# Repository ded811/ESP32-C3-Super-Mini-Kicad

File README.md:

# ESP32-C3 Super Mini KiCad Schematic

An ESP32-C3 Super Mini KiCad Schematic based on the AliExpress ESP32-C3 Super Mini boards, with the following improvements over the original design.

## Improvements

### Antenna — Major Improvement

| | Original | This Design |
|---|---|---|
| **Part** | CrossAir CA-C03 | Johanson 2450AT18A100 |
| **Frequency** | 2.7 GHz (mistuned for 2.4 GHz use) | 2.4 GHz (properly tuned) |
| **Matching Network** | None | Full T-network |
| **Placement** | Poorly placed | Optimised |

The original design used a **CrossAir CA-C03** antenna — a 2.7 GHz antenna pressed into service at 2.4 GHz with no matching network. The result is a mistuned antenna with poor radiation efficiency.

This design replaces it with a **Johanson 2450AT18A100**, a proper 2.4 GHz chip antenna, paired with a full T-network matching circuit using Murata 0201 RF components:

```
RF feed → 2.7 nH (series) → 1.0 pF (shunt to GND) → 3.9 nH (series) → Antenna
```

This ensures the antenna is correctly matched to 50 Ω at 2.4 GHz, maximising radiated power and receiver sensitivity for Wi-Fi and Bluetooth operation.

## License

This work is licensed under a [Creative Commons Attribution 4.0 International License (CC BY 4.0)](https://creativecommons.org/licenses/by/4.0/).

You are free to share and adapt this material for any purpose, provided appropriate credit is given.

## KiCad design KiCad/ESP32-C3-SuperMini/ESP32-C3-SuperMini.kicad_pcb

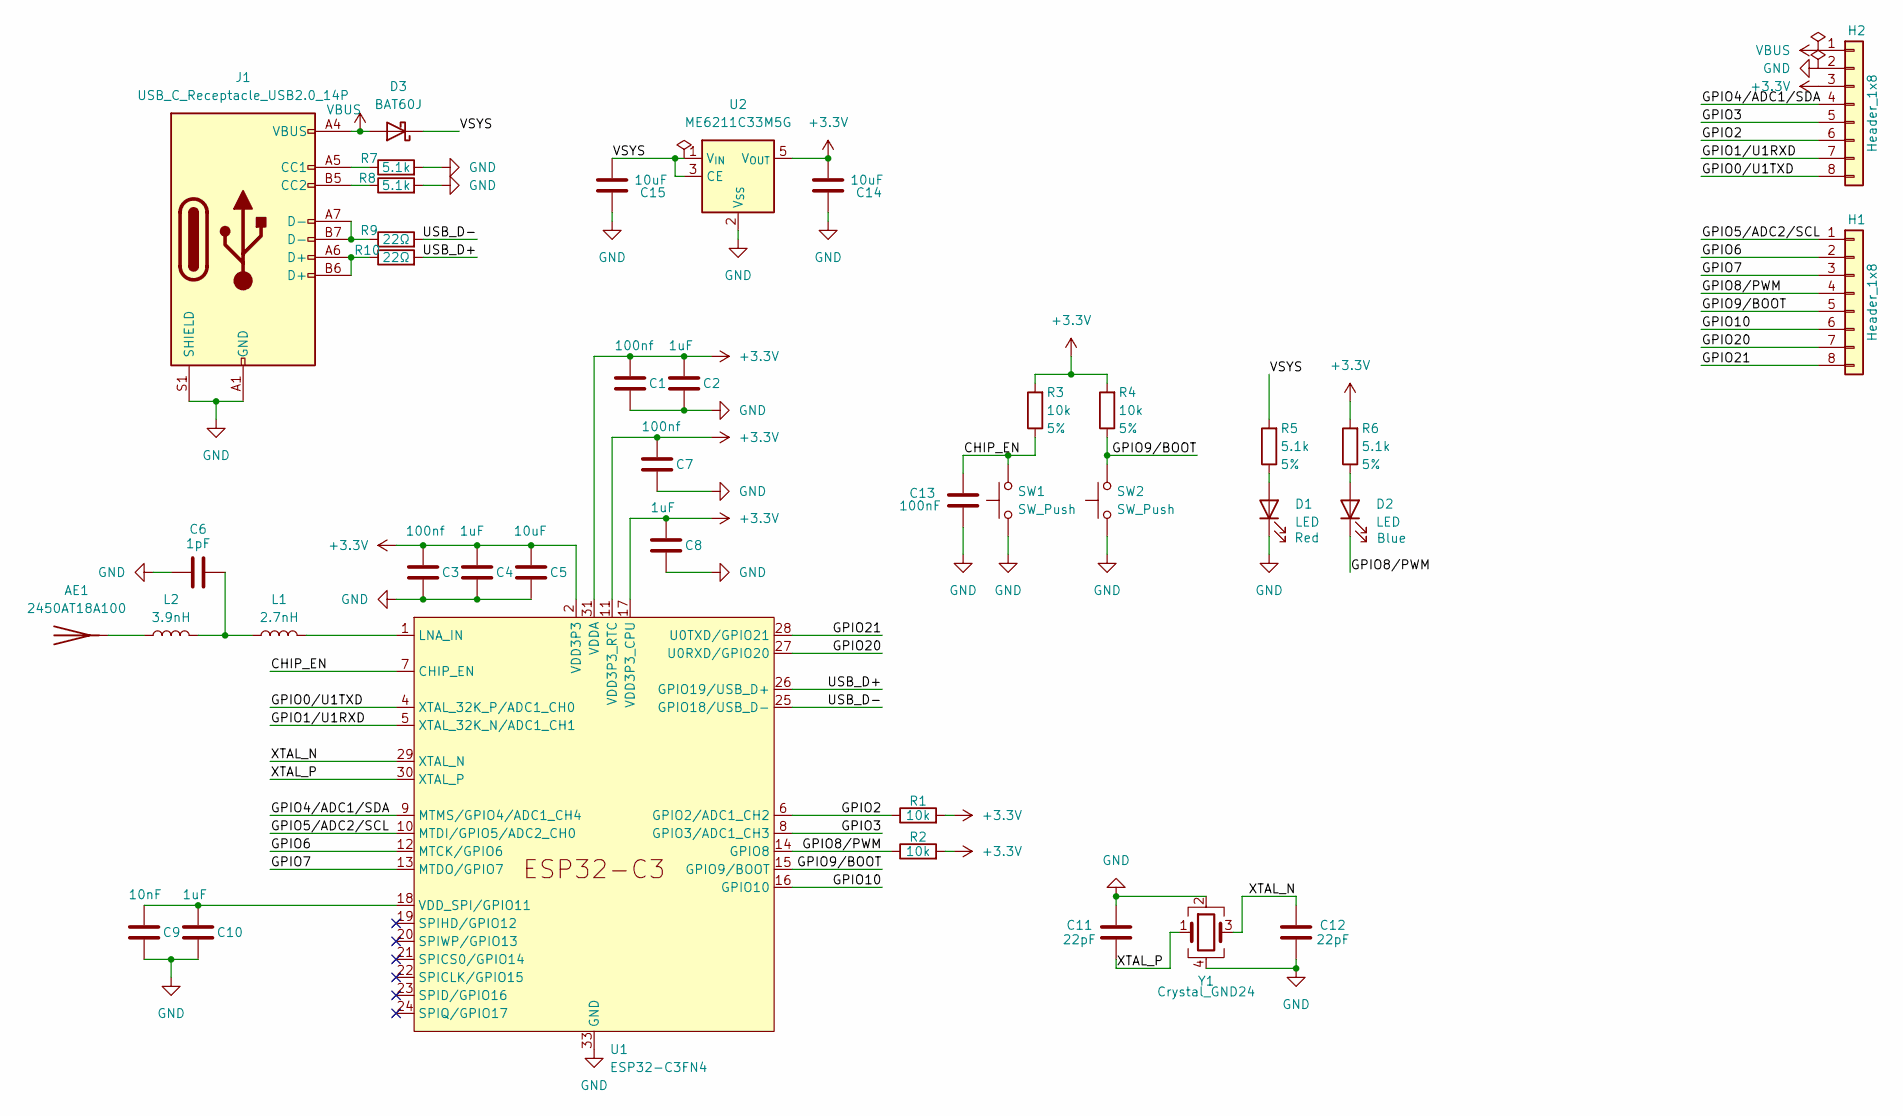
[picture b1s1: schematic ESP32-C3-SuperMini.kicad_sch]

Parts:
AE1: 2450AT18A100; Johanson_2450AT18x100; MPN 2450AT18A0100001; LCSC C89334
C1, C3, C7: 100nf; C_0201_0603Metric; Tolerance 10%; Voltage 10V; LCSC C76934
C2, C4, C8, C10: 1uF; C_0201_0603Metric; Tolerance 10%; Voltage 10V; LCSC C2846675
C5, C15: 10uF; C_0402_1005Metric; Tolerance 10%; Voltage 10V; LCSC C315248
C6: 1pF; C_0201_0603Metric; Tolerance ±0.1pF; Voltage 10V; LCSC C85893
C9: 10nF; C_0201_0603Metric; Tolerance 10%; Voltage 10V; LCSC C76941
C11: 22pF; C_0201_0603Metric; Tolerance 10%; Voltage 16V; LCSC C115548
C12: 22pF; C_0201_0603Metric; Tolerance 10%; Voltage 10V; LCSC C115548
C13: 100nF; C_0201_0603Metric; Tolerance 10%; Voltage 10V; LCSC C76934
C14: 10uF; C_0402_1005Metric; Tolerance 20%; Voltage 10V; LCSC C315248
D1: LED; LED_0603_1608Metric; MPN KT-0603R; LCSC C2286
D2: LED; LED_0603_1608Metric; MPN KT-0603B; LCSC C2287
D3: BAT60J; D_SOD-323; MPN BAT60J; LCSC C116046
H1, H2: Header_1x8; PinHeader_1x08_P2.54mm_Vertical_EdgeMount_Castellated
J1: USB_C_Receptacle_USB2.0_14P; USB_C_Receptacle_HRO_TYPE-C-31-M-12; MPN TYPE-C 16PIN 2MD(073); LCSC C2765186
L1: 2.7nH; L_0201_0603Metric; Tolerance 2%; LCSC C98043
L2: 3.9nH; L_0201_0603Metric; Tolerance 2%; LCSC C77115
R1, R2, R3, R4: 10k; R_0201_0603Metric; Tolerance 5%; LCSC C4332048
R5, R6, R7, R8: 5.1k; R_0201_0603Metric; Tolerance 5%; LCSC C25837
R9, R10: 22Ω; R_0201_0603Metric; Tolerance 5%; LCSC C270355
SW1, SW2: SW_Push; SW_SPST_B3U-1000P; MPN HX 3x4x2-1.6N; LCSC C49234124
U1: ESP32-C3FN4; QFN-32-1EP_5x5mm_P0.5mm_EP3.45x3.45mm; LCSC C2848860
U2: ME6211C33M5G; SOT-23-5; MPN ME6211C33M5G; LCSC C82942
Y1: Crystal_GND24; Crystal_SMD_3225-4Pin_3.2x2.5mm; Tolerance ±10ppm; MPN X322540MPB4SI; LCSC C9010

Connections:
+3.3V: C1.1, C2.1, C3.1, C4.1, C5.1, C7.1, C8.1, C14.1, H2.3, R1.2, R2.2, R3.2, R4.2, R6.2, U1.2 (VDD3P3), U1.3 (VDD3P3), U1.11 (VDD3P3_RTC), U1.17 (VDD3P3_CPU), U1.31 (VDDA), U1.32 (VDDA), U2.5 (V_{OUT})
/CHIP_EN: C13.2, R3.1, SW1.2, U1.7 (CHIP_EN)
/GPIO0/U1TXD: H2.8, U1.4 (XTAL_32K_P/ADC1_CH0)
/GPIO1/U1RXD: H2.7, U1.5 (XTAL_32K_N/ADC1_CH1)
/GPIO2: H2.6, R1.1, U1.6 (GPIO2/ADC1_CH2)
/GPIO3: H2.5, U1.8 (GPIO3/ADC1_CH3)
/GPIO4/ADC1/SDA: H2.4, U1.9 (MTMS/GPIO4/ADC1_CH4)
/GPIO5/ADC2/SCL: H1.1, U1.10 (MTDI/GPIO5/ADC2_CH0)
/GPIO6: H1.2, U1.12 (MTCK/GPIO6)
/GPIO7: H1.3, U1.13 (MTDO/GPIO7)
/GPIO8/PWM: D2.1 (K), H1.4, R2.1, U1.14 (GPIO8)
/GPIO9/BOOT: H1.5, R4.1, SW2.2, U1.15 (GPIO9/BOOT)
/GPIO10: H1.6, U1.16 (GPIO10)
/GPIO20: H1.7, U1.27 (U0RXD/GPIO20)
/GPIO21: H1.8, U1.28 (U0TXD/GPIO21)
/USB_D+: R10.2, U1.26 (GPIO19/USB_D+)
/USB_D-: R9.2, U1.25 (GPIO18/USB_D-)
/VSYS: C15.1, D3.1 (K), R5.2, U2.1 (V_{IN}), U2.3 (CE)
/XTAL_N: C12.2, U1.29 (XTAL_N), Y1.3
/XTAL_P: C11.2, U1.30 (XTAL_P), Y1.1
GND: C1.2, C2.2, C3.2, C4.2, C5.2, C6.2, C7.2, C8.2, C9.2, C10.2, C11.1, C12.1, C13.1, C14.2, C15.2, D1.1 (K), H2.2, J1.A1 (GND), J1.A12 (GND), J1.B1 (GND), J1.B12 (GND), J1.S1 (SHIELD), R7.2, R8.2, SW1.1, SW2.1, U1.33 (GND), U2.2 (V_{SS}), Y1.2, Y1.4
unnamed: AE1.1 (A), L2.1
unnamed: C6.1, L1.1, L2.2
unnamed: D1.2 (A), R5.1
unnamed: D2.2 (A), R6.1
unnamed: J1.A5 (CC1), R7.1
unnamed: J1.B5 (CC2), R8.1
unnamed: J1.A6 (D+), J1.B6 (D+), R10.1
unnamed: J1.A7 (D-), J1.B7 (D-), R9.1
unnamed: L1.2, U1.1 (LNA_IN)
unnamed: C9.1, C10.1, U1.18 (VDD_SPI/GPIO11)
VBUS: D3.2 (A), H2.1, J1.A4 (VBUS), J1.A9 (VBUS), J1.B4 (VBUS), J1.B9 (VBUS)

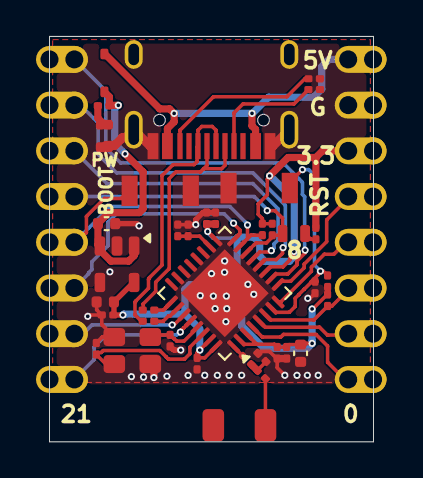
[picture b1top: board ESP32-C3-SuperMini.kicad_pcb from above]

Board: 2 copper layers, 18.0 x 22.5 mm, 39 parts (0 on the bottom side), 32 nets.

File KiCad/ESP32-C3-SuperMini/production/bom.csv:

Designator,Footprint,Quantity,Value,LCSC Part #
AE1,Johanson_2450AT18x100,1,2450AT18A100,2450AT18A0100001
"C1, C13, C3, C7",0201,4,100nf,
"C10, C2, C4, C8",0201,4,1uF,
"C11, C12",0201,2,22pF,
"C14, C15, C5",0402,3,10uF,
C6,0201,1,1pF,
C9,0201,1,10nF,
D1,0603,1,LED,C2286
D2,0603,1,LED,C2287
D3,D_SOD-323,1,BAT60J,C116046
"H1, H2",PinHeader_1x08_P2.54mm_Vertical_EdgeMount_Castellated,2,Header_1x8,
J1,USB_C_Receptacle_HRO_TYPE-C-31-M-12,1,USB_C_Receptacle_USB2.0_14P,C2765186
L1,0201,1,2.7nH,
L2,0201,1,3.9nH,
"R1, R2, R3, R4",0201,4,10k,
"R10, R9",0201,2,22Ω,
"R5, R6, R7, R8",0201,4,5.1k,
"SW1, SW2",SW_SPST_B3U-1000P,2,SW_Push,C49234124
U1,QFN-32-1EP_5x5mm_P0.5mm_EP3.45x3.45mm,1,ESP32-C3,
U2,SOT-23-5,1,ME6211C33M5G,C82942
Y1,Crystal_SMD_3225-4Pin_3.2x2.5mm,1,Crystal_GND24,C9010

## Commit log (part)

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2026-04-27 Initial plan
2026-04-27 Changes before error encountered
    Agent-Logs-Url: https://github.com/ded811/-ESP32-C3-Super-Mini-Kicad/sessions/79b2372a-bc80-4f83-b0c6-4d7ae2bd8e26
2026-04-27 wip files
